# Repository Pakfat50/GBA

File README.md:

# GBA
Ground Balloon Anemometer

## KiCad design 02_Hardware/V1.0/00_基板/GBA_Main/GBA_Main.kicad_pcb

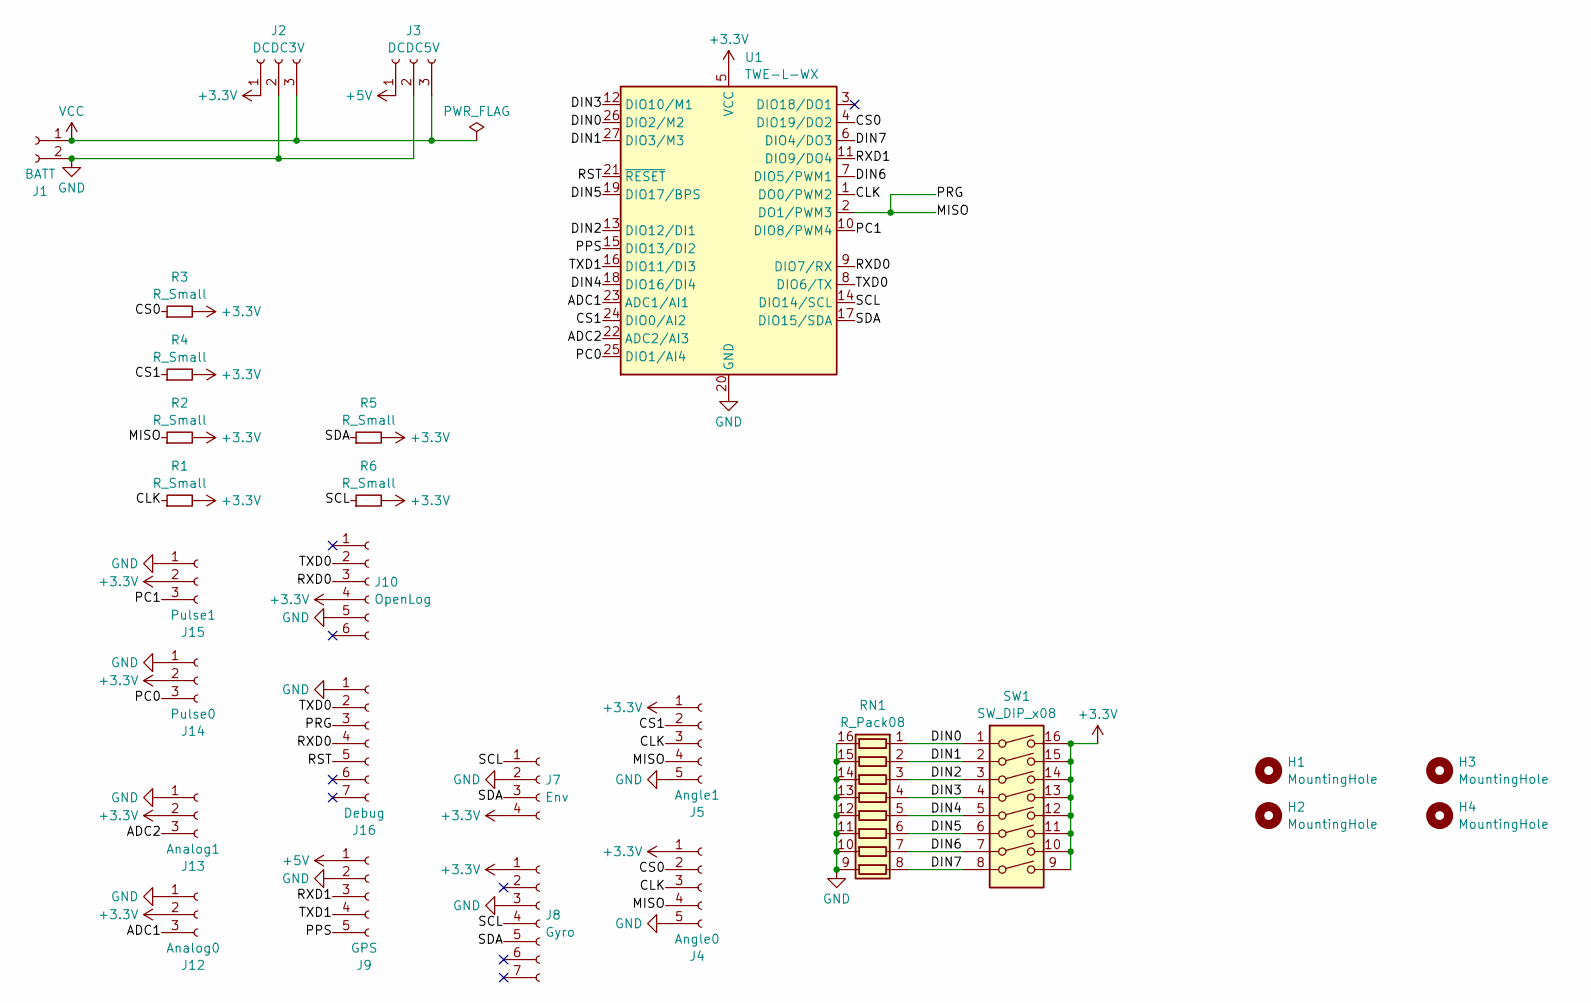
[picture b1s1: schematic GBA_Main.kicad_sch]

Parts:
H1, H2, H3, H4: MountingHole; MountingHole_3.5mm
J1: BATT; JST_XH_S2B-XH-A-1_1x02_P2.50mm_Horizontal
J2: DCDC3V; PinHeader_1x03_P2.54mm_Vertical
J3: DCDC5V; PinHeader_1x03_P2.54mm_Vertical
J4: Angle0; PinSocket_1x05_P2.00mm_Vertical
J5: Angle1; PinSocket_1x05_P2.00mm_Vertical
J7: Env; PinHeader_1x04_P2.54mm_Vertical
J8: Gyro; PinHeader_1x07_P2.54mm_Vertical
J9: GPS; PinHeader_1x05_P2.54mm_Vertical
J10: OpenLog; PinSocket_1x06_P2.54mm_Horizontal
J12: Analog0; PinSocket_1x03_P2.54mm_Vertical
J13: Analog1; PinSocket_1x03_P2.54mm_Vertical
J14: Pulse0; PinSocket_1x03_P2.54mm_Vertical
J15: Pulse1; PinSocket_1x03_P2.54mm_Vertical
J16: Debug; PinSocket_1x07_P2.54mm_Horizontal
R1, R2, R3, R4, R5, R6: R_Small; R_0603_1608Metric
RN1: R_Pack08; EXB2HV_1
SW1: SW_DIP_x08; DIP-16_W7.62mm
U1: TWE-L-WX; MonoWireless_TWE-L-WX

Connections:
+3.3V: J2.1, J4.1, J5.1, J7.4, J8.1, J10.4, J12.2, J13.2, J14.2, J15.2, R1.2, R2.2, R3.2, R4.2, R5.2, R6.2, SW1.9, SW1.10, SW1.11, SW1.12, SW1.13, SW1.14, SW1.15, SW1.16, U1.5 (VCC)
+5V: J3.1, J9.1
/ADC1: J12.3, U1.23 (ADC1/AI1)
/ADC2: J13.3, U1.22 (ADC2/AI3)
/CLK: J4.3, J5.3, R1.1, U1.1 (DO0/PWM2)
/CS0: J4.2, R3.1, U1.4 (DIO19/DO2)
/CS1: J5.2, R4.1, U1.24 (DIO0/AI2)
/DIN0: RN1.1 (R1.1), SW1.1, U1.26 (DIO2/M2)
/DIN1: RN1.2 (R2.1), SW1.2, U1.27 (DIO3/M3)
/DIN2: RN1.3 (R3.1), SW1.3, U1.13 (DIO12/DI1)
/DIN3: RN1.4 (R4.1), SW1.4, U1.12 (DIO10/M1)
/DIN4: RN1.5 (R5.1), SW1.5, U1.18 (DIO16/DI4)
/DIN5: RN1.6 (R6.1), SW1.6, U1.19 (DIO17/BPS)
/DIN6: RN1.7 (R7.1), SW1.7, U1.7 (DIO5/PWM1)
/DIN7: RN1.8 (R8.1), SW1.8, U1.6 (DIO4/DO3)
/MISO: J4.4, J5.4, J16.3, R2.1, U1.2 (DO1/PWM3)
/PC0: J14.3, U1.25 (DIO1/AI4)
/PC1: J15.3, U1.10 (DIO8/PWM4)
/PPS: J9.5, U1.15 (DIO13/DI2)
/RST: J16.5, U1.21 (~RESET)
/RXD0: J10.3, J16.4, U1.9 (DIO7/RX)
/RXD1: J9.3, U1.11 (DIO9/DO4)
/SCL: J7.1, J8.4, R6.1, U1.14 (DIO14/SCL)
/SDA: J7.3, J8.5, R5.1, U1.17 (DIO15/SDA)
/TXD0: J10.2, J16.2, U1.8 (DIO6/TX)
/TXD1: J9.4, U1.16 (DIO11/DI3)
GND: J1.2, J2.2, J3.2, J4.5, J5.5, J7.2, J8.3, J9.2, J10.5, J12.1, J13.1, J14.1, J15.1, J16.1, RN1.9 (R8.2), RN1.10 (R7.2), RN1.11 (R6.2), RN1.12 (R5.2), RN1.13 (R4.2), RN1.14 (R3.2), RN1.15 (R2.2), RN1.16 (R1.2), U1.20 (GND), U1.28 (GND), U1.30 (GND), U1.31 (GND), U1.32 (GND)
VCC: J1.1, J2.3, J3.3

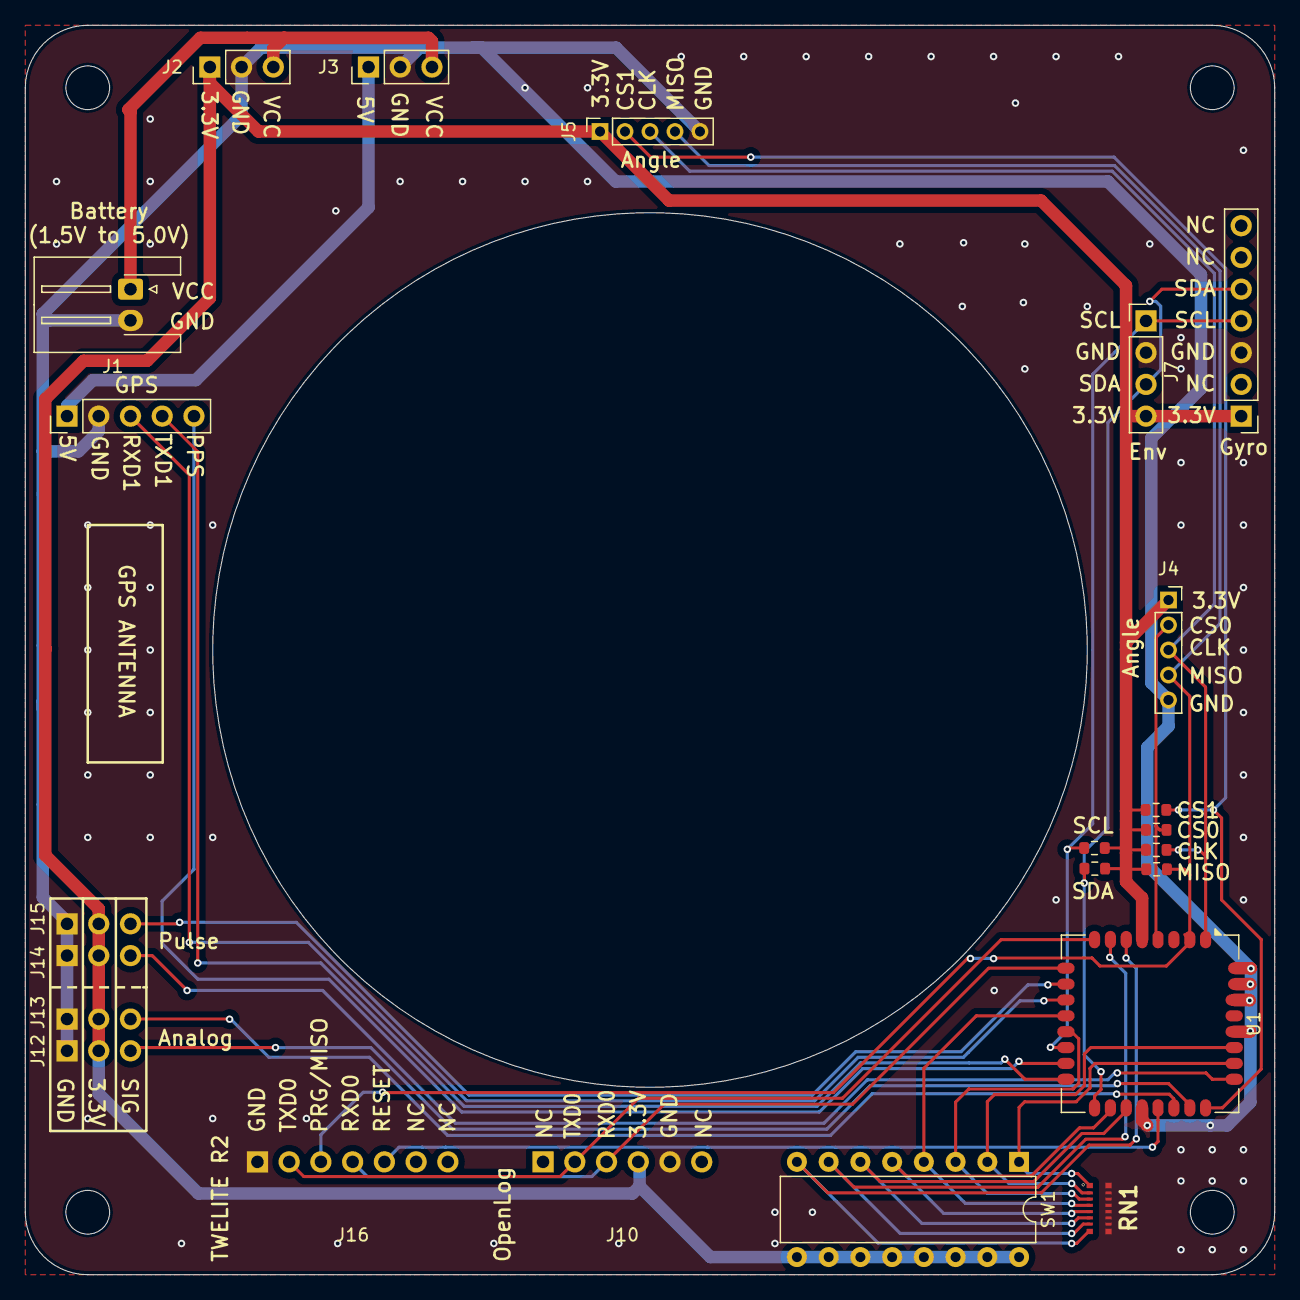
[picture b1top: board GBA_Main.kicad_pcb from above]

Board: 2 copper layers, 100.0 x 100.0 mm, 27 parts (0 on the bottom side), 28 nets.

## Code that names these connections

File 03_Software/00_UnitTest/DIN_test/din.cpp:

#include <TWELITE>
#include "din.h"

void dinInit(void){
    pinMode(DIN_PIN0, PIN_MODE::INPUT); //DIN0
    pinMode(DIN_PIN1, PIN_MODE::INPUT); //DIN1
    pinMode(DIN_PIN2, PIN_MODE::INPUT); //DIN2
    pinMode(DIN_PIN3, PIN_MODE::INPUT); //DIN3
    pinMode(DIN_PIN4, PIN_MODE::INPUT); //DIN4
    pinMode(DIN_PIN5, PIN_MODE::INPUT); //DIN5
    pinMode(DIN_PIN6, PIN_MODE::INPUT); //DIN6
    pinMode(DIN_PIN7, PIN_MODE::INPUT); //DIN7
}

uint8_t getChannel(void){
    uint8_t din0, din1, din2, din3;
    uint8_t channel = 0;

    din0 = (digitalRead(DIN_PIN0) == HIGH) ? 1: 0;
    din1 = (digitalRead(DIN_PIN1) == HIGH) ? 1: 0;
    din2 = (digitalRead(DIN_PIN2) == HIGH) ? 1: 0;
    din3 = (digitalRead(DIN_PIN3) == HIGH) ? 1: 0;

    channel  = din3;
    channel |= din2<<1;
    channel |= din1<<2;
    channel |= din0<<3;

    return channel;

}

uint8_t getSensorId(void){
    uint8_t din4, din5, din6, din7;
    uint8_t sensor_id = 0;

    din4 = (digitalRead(DIN_PIN4) == HIGH) ? 1: 0;
    din5 = (digitalRead(DIN_PIN5) == HIGH) ? 1: 0;
    din6 = (digitalRead(DIN_PIN6) == HIGH) ? 1: 0;
    din7 = (digitalRead(DIN_PIN7) == HIGH) ? 1: 0;

    sensor_id  = din7;
    sensor_id |= din6<<1;
    sensor_id |= din5<<2;
    sensor_id |= din4<<3;

    return sensor_id;
}
